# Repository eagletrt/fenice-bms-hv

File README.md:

# Fenice BMS - hardware

## Libraries
The projects don't include the libraries since they use the KiCAD official ones.
Set accordingly the variables `${KICAD_SYMBOL_DIR}` and `${KISYSMOD}` for 
`kicad-symbols` and `kicad-footprints` respectively.
**For `kicad-symbols` checkout the repo to `v5` for now to have the legacy ones.**

Don't rescue symbols!

## Repo structure
```
fenice-bms-hv:hw-master
|-- docs/       # Docs and datasheets of common interest
|-- mainboard/  # MainBoard hardware project folder
|-- cellboard/  # CellBoard hardware project folder
```

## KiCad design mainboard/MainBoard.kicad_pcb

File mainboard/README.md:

# MainBoard
Formula SAE - unitn

## Authors
Latest first:
- Filippo Volpe
- Franco Tabarelli
- Not clear

## Project structure
```
mainboard/
|-- MainBoard.pro           # Project file
|-- MainBoard.sch           # Schematic root
|-- MainShutdown.sch        # Analog shutdown logic schematic
|-- MCU.sch                 # MCU schematic
|-- HVSide.sch              # High voltage monitoring schematic
|-- MainBoard.kicad_pcb     # Board layout file
|-- MainBoard-cache.lib     # Local cache of symbols
|-- fp-info-cache           # Cache of footprints
|-- fp-lib-table            # List of footprint lib files
|-- sym-lib-table           # List of symbols lib files
|-- gerber/                 # Gerbers outputs
|-- netlists/               # Netlists outputs
|-- images/                 # Board renders and such
|-- docs/                   # Additional related documents and outputs
|   |-- hv-bms-mainboard.md # Report/documentation
|-- bom/                    # BOM folder
```

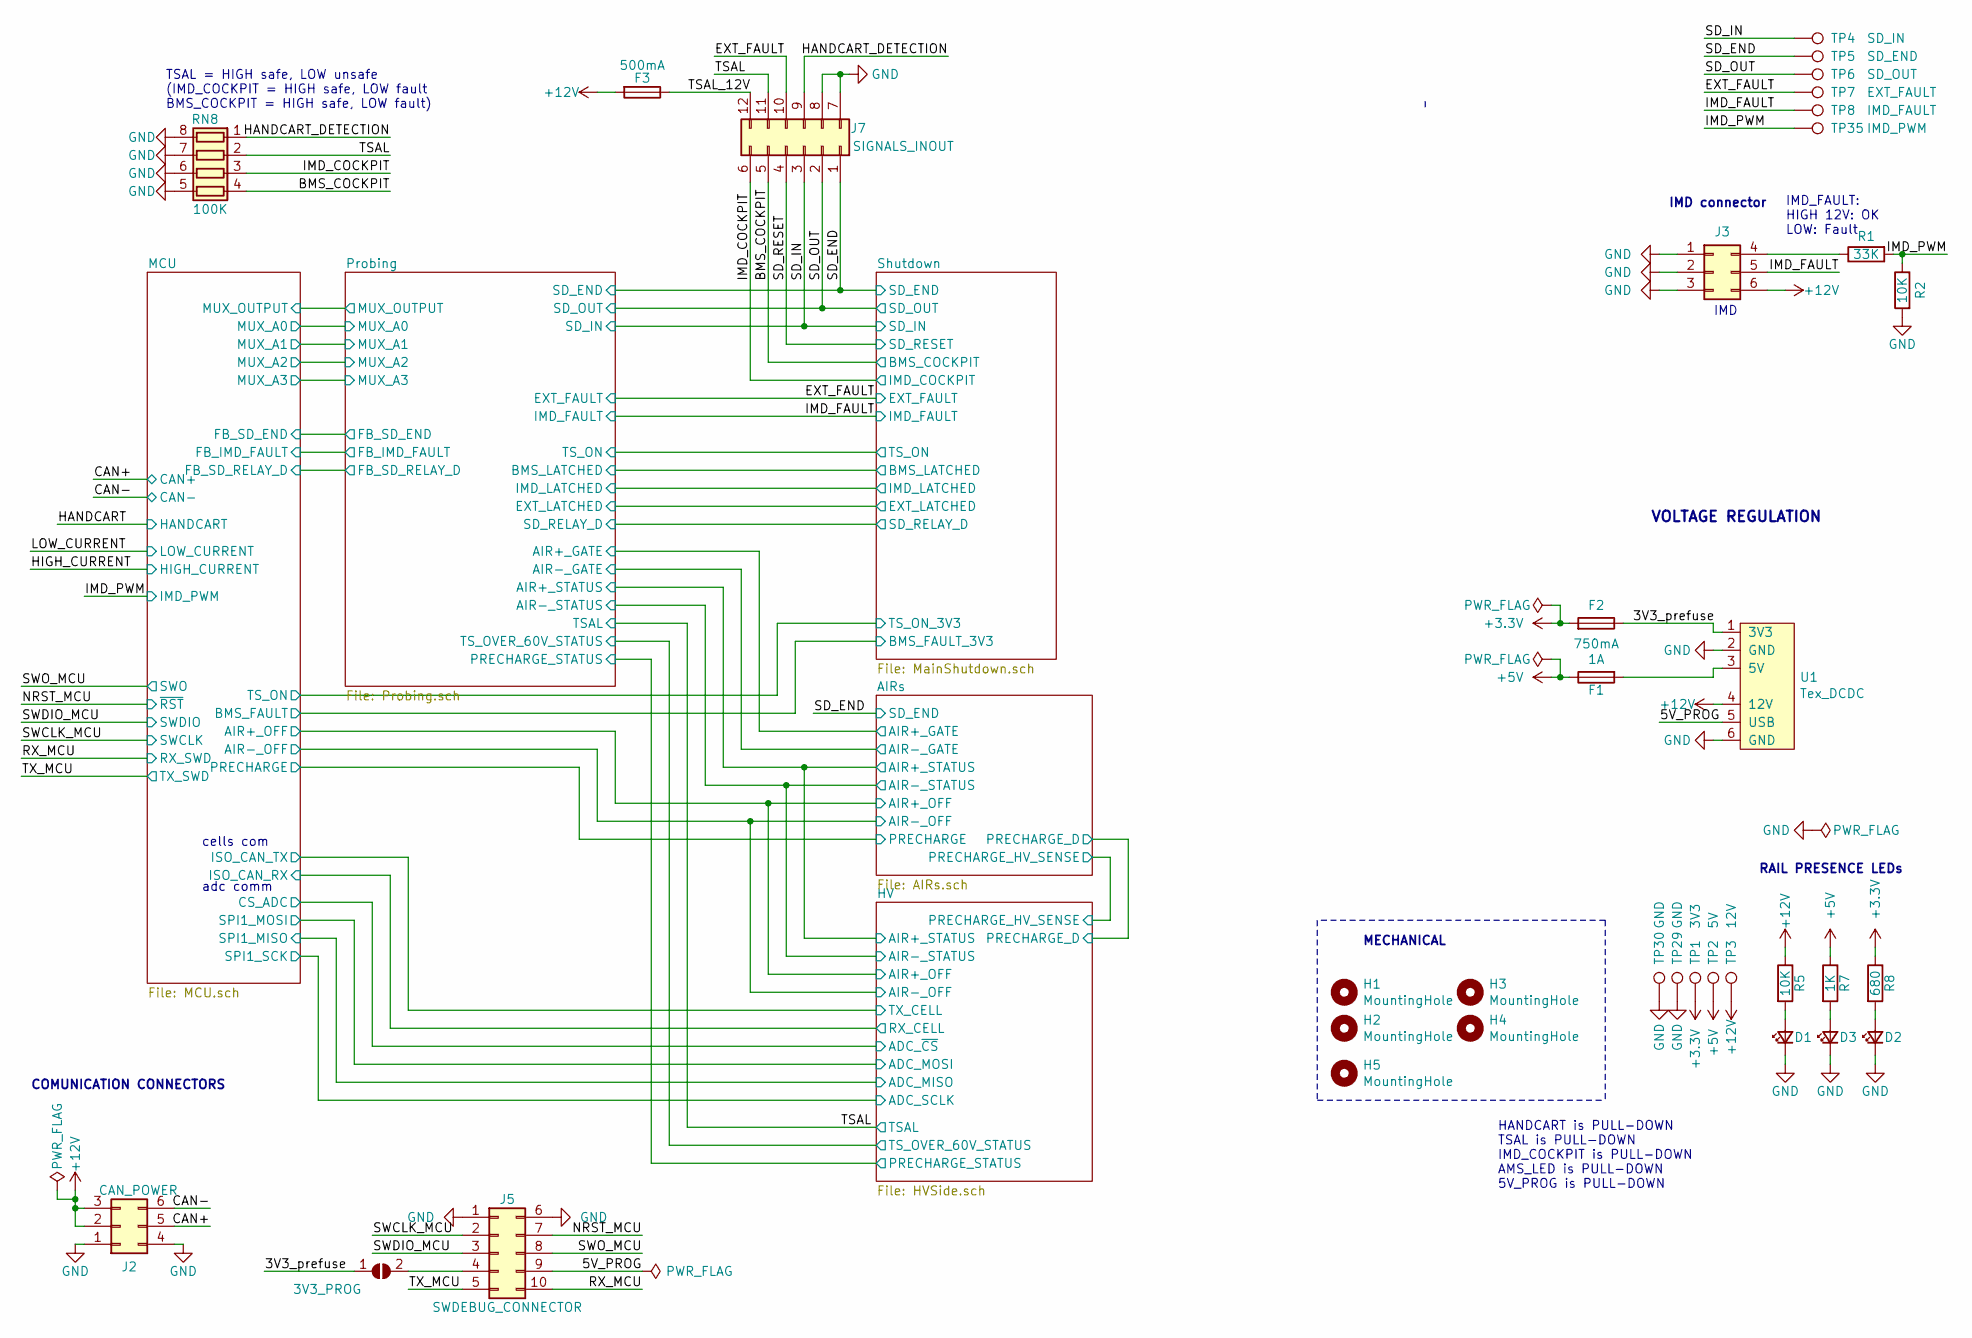
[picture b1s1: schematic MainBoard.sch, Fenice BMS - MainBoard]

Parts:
D1, D2, D3: LED_Small; LED_0603_1608Metric_Castellated
F1: 1A; Fuse_0805_2012Metric
F2: 750mA; Fuse_0805_2012Metric
F3: 500mA; Fuse_1812_4532Metric
H1, H2, H3, H4, H5: MountingHole; MountingHole_3.2_6.1Free
J2: CAN_POWER; Molex_Micro-Fit_3.0_43045-0612_2x03_P3.00mm_Vertical
J3: CONN_2X3; Molex_Micro-Fit_3.0_43045-0612_2x03_P3.00mm_Vertical
J5: SWDEBUG_CONNECTOR; Molex_Nano-Fit_105310-xx10_2x05_P2.50mm_Vertical
J7: SIGNALS_INOUT; Molex_Micro-Fit_3.0_43045-1212_2x06_P3.00mm_Vertical
JP2: 3V3_PROG; SolderJumper-2_P1.3mm_Open_RoundedPad1.0x1.5mm
R1: 33K; R_0603_1608Metric
R2, R5: 10K; R_0603_1608Metric
R7: 1K; R_0603_1608Metric
R8: 680; R_0603_1608Metric
RN8: 100K; R_Array_Convex_4x0603
TP1: 3V3; TestPoint_Pad_D1.0mm
TP2: 5V; TestPoint_Pad_D1.0mm
TP3: 12V; TestPoint_Pad_D1.0mm
TP4: SD_IN; TestPoint_Pad_D1.0mm
TP5: SD_END; TestPoint_Pad_D1.0mm
TP6: SD_OUT; TestPoint_Pad_D1.0mm
TP7: EXT_FAULT; TestPoint_Pad_D1.0mm
TP8: IMD_FAULT; TestPoint_Pad_D1.0mm
TP29, TP30: GND; TestPoint_GNDedge
TP35: IMD_PWM; TestPoint_Pad_D1.0mm
U1: Tex_DCDC; Tex_DCDC_vertical_up

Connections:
+5V: F1.1, R7.1, TP2.1; also elsewhere on the board
+12V: F3.2, J2.2, J2.3, J3.6, R5.1, TP3.1, U1.4 (12V); also elsewhere on the board
/3V3_prefuse: F2.1, JP2.1 (A), U1.1 (3V3)
/5V_PROG: J5.9, U1.5 (USB)
/BMS_COCKPIT: J7.5, RN8.4 (R4.1); also elsewhere on the board
/CAN+: J2.5; also elsewhere on the board
/CAN-: J2.6; also elsewhere on the board
/EXT_FAULT: J7.10, TP7.1; also elsewhere on the board
/HANDCART_DETECTION: J7.9, RN8.1 (R1.1)
/IMD_COCKPIT: J7.6, RN8.3 (R3.1); also elsewhere on the board
/IMD_FAULT: J3.5, TP8.1; also elsewhere on the board
/IMD_PWM: R1.2, R2.1, TP35.1; also elsewhere on the board
/NRST_MCU: J5.7; also elsewhere on the board
/RX_MCU: J5.10; also elsewhere on the board
/SD_END: J7.1, TP5.1; also elsewhere on the board
/SD_IN: J7.3, TP4.1; also elsewhere on the board
/SD_OUT: J7.2, TP6.1; also elsewhere on the board
/SD_RESET: J7.4; also elsewhere on the board
/SWCLK_MCU: J5.2; also elsewhere on the board
/SWDIO_MCU: J5.3; also elsewhere on the board
/SWO_MCU: J5.8; also elsewhere on the board
/TSAL: J7.11, RN8.2 (R2.1); also elsewhere on the board
/TSAL_12V: F3.1, J7.12
/TX_MCU: J5.5; also elsewhere on the board
GND: D1.1 (K), D2.1 (K), D3.1 (K), J2.1, J2.4, J3.1, J3.2, J3.3, J5.1, J5.6, J7.7, J7.8, R2.2, RN8.5 (R4.2), RN8.6 (R3.2), RN8.7 (R2.2), RN8.8 (R1.2), TP29.1, TP30.1, U1.2 (GND), U1.6 (GND); also elsewhere on the board
unnamed: D1.2 (A), R5.2
unnamed: D2.2 (A), R8.2
unnamed: D3.2 (A), R7.2
unnamed: F1.2, U1.3 (5V)
unnamed: J3.4, R1.1
unnamed: J5.4, JP2.2 (B)

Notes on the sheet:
IMD
IMD connector
COMUNICATION CONNECTORS
MECHANICAL
IMD_FAULT: HIGH 12V: OK LOW: Fault
adc comm
TSAL = HIGH safe, LOW unsafe (IMD_COCKPIT = HIGH safe, LOW fault BMS_COCKPIT = HIGH safe, LOW fault)
cells com
HANDCART is PULL-DOWN TSAL is PULL-DOWN IMD_COCKPIT is PULL-DOWN AMS_LED is PULL-DOWN 5V_PROG is PULL-DOWN
VOLTAGE REGULATION
RAIL PRESENCE LEDs

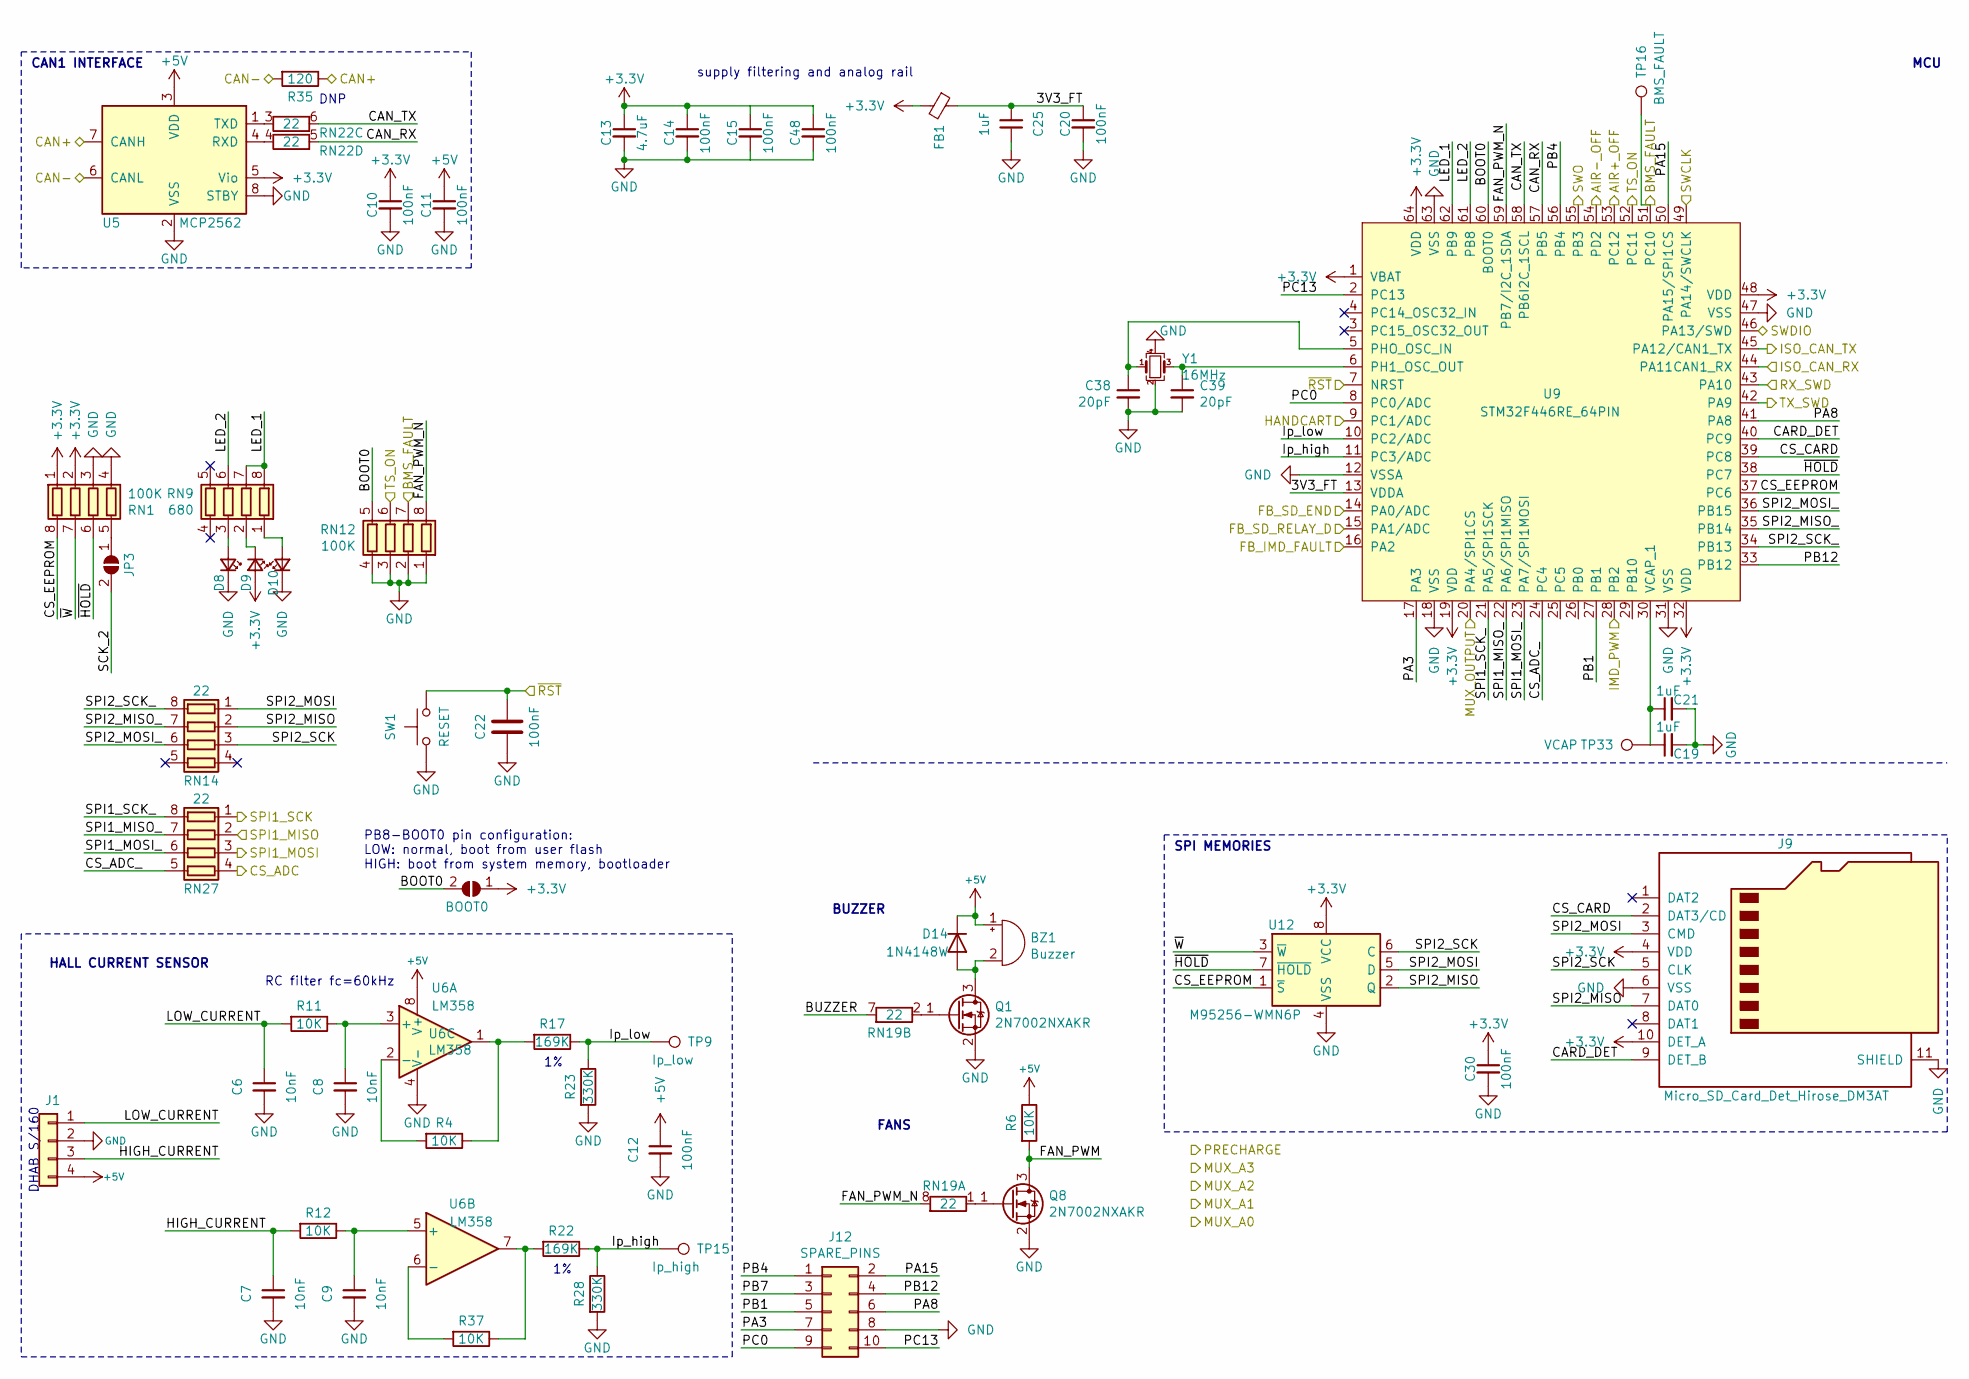
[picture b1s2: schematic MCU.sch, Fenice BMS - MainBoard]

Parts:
BZ1: Buzzer; Buzzer_TDK_SD1614TT_D16mm_H14mm_P5mm
C6, C7, C8, C9: 10nF; C_0603_1608Metric
C10, C11, C12, C14, C15, C20, C22, C30, C48: 100nF; C_0603_1608Metric
C13: 4.7uF; C_0805_2012Metric
C19, C21, C25: 1uF; C_0805_2012Metric
C38, C39: 20pF; C_0603_1608Metric
D8: LED_Small; LED_reverse_mount_cilindrical
D9, D10: LED_Small; LED_0603_1608Metric_Castellated
D14: 1N4148W; D_SOD-123
FB1: FerriteBead_Small; L_0603_1608Metric_Pad1.05x0.95mm_HandSolder
J1: CONN_1x4; Molex_Micro-Fit_3.0_43650-0415_1x04_P3.00mm_Vertical
J9: Micro_SD_Card_Det_Hirose_DM3AT; microSD_HC_Hirose_DM3AT-SF-PEJM5
J12: SPARE_PINS; PinHeader_2x05_P2.54mm_Vertical
JP1: BOOT0; SolderJumper-2_P1.3mm_Open_RoundedPad1.0x1.5mm
JP3: SolderJumper_2_Open; SolderJumper-2_P1.3mm_Open_RoundedPad1.0x1.5mm
Q1, Q8: 2N7002NXAKR; SOT-23
R4, R6, R11, R12, R37: 10K; R_0603_1608Metric
R17, R22: 169K; R_0603_1608Metric
R23, R28: 330K; R_0603_1608Metric
R35: 120; R_0805_2012Metric
RN1, RN12: 100K; R_Array_Convex_4x0603
RN9: 680; R_Array_Convex_4x0603
RN14, RN19, RN22, RN27: 22; R_Array_Convex_4x0603
SW1: RESET; SW_SPST_FSMSM
TP9: Ip_low; TestPoint_Pad_D1.0mm
TP15: Ip_high; TestPoint_Pad_D1.0mm
TP16: BMS_FAULT; TestPoint_Pad_D1.0mm
TP33: VCAP; TestPoint_Pad_D1.0mm
U5: MCP2562; SOIC-8_3.9x4.9mm_P1.27mm
U6: LM358; TSOT-23-8
U9: STM32F446RE_64PIN; LQFP-64_10x10mm_P0.5mm
U12: M95256-WMN6P; TSSOP-8_4.4x3mm_P0.65mm
Y1: 16MHz; Crystal_SMD_3225-4Pin_3.2x2.5mm

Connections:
+5V: BZ1.1 (-), C11.1, C12.1, D14.1 (K), J1.4, R6.1, U5.3 (VDD), U6.8 (V+); also elsewhere on the board
/AIRs/AIR+_OFF: U9.53 (PC12); also elsewhere on the board
/AIRs/AIR-_OFF: U9.54 (PD2); also elsewhere on the board
/CAN+: R35.1, U5.7 (CANH); also elsewhere on the board
/CAN-: R35.2, U5.6 (CANL); also elsewhere on the board
/HANDCART: U9.9 (PC1/ADC)
/HV/ADC_MISO: RN27.2 (R2.1); also elsewhere on the board
/HV/ADC_MOSI: RN27.3 (R3.1); also elsewhere on the board
/HV/ADC_SCLK: RN27.1 (R1.1); also elsewhere on the board
/HV/ADC_~CS~: RN27.4 (R4.1); also elsewhere on the board
/IMD_PWM: U9.28 (PB2); also elsewhere on the board
/MCU/3V3_FT: C20.1, C25.2, FB1.1, U9.13 (VDDA)
/MCU/BMS_FAULT: RN12.7 (R2.2), TP16.1, U9.51 (PC10); also elsewhere on the board
/MCU/BOOT0: JP1.2 (B), RN12.5 (R4.2), U9.60 (BOOT0)
/MCU/BUZZER: RN19.7 (R2.2)
/MCU/CAN_RX: RN22.5 (R4.2), U9.57 (PB5)
/MCU/CAN_TX: RN22.6 (R3.2), U9.58 (PB6I2C_1SCL)
/MCU/CARD_DET: J9.9 (DET_B), U9.40 (PC9)
/MCU/CS_ADC_: RN27.5 (R4.2), U9.24 (PC4)
/MCU/CS_CARD: J9.2 (DAT3/CD), U9.39 (PC8)
/MCU/CS_EEPROM: RN1.8 (R1.2), U9.37 (PC6), U12.1 (~S)
/MCU/FAN_PWM: Q8.3 (D), R6.2
/MCU/FAN_PWM_N: RN12.8 (R1.2), RN19.8 (R1.2), U9.59 (PB7/I2C_1SDA)
/MCU/FB_IMD_FAULT: U9.16 (PA2)
/MCU/FB_SD_END: U9.14 (PA0/ADC); also elsewhere on the board
/MCU/FB_SD_RELAY_D: U9.15 (PA1/ADC)
/MCU/HIGH_CURRENT: C7.1, J1.3, R12.2
/MCU/ISO_CAN_RX: U9.44 (PA11CAN1_RX); also elsewhere on the board
/MCU/ISO_CAN_TX: U9.45 (PA12/CAN1_TX); also elsewhere on the board
/MCU/Ip_high: R22.1, R28.1, TP15.1, U9.11 (PC3/ADC)
/MCU/Ip_low: R17.1, R23.1, TP9.1, U9.10 (PC2/ADC)
/MCU/LED_1: RN9.7 (R2.2), RN9.8 (R1.2), U9.62 (PB9)
/MCU/LED_2: RN9.6 (R3.2), U9.61 (PB8)
/MCU/LOW_CURRENT: C6.1, J1.1, R11.2
/MCU/MUX_OUTPUT: U9.20 (PA4/SPI1CS); also elsewhere on the board
/MCU/PA3: J12.7, U9.17 (PA3)
/MCU/PA8: J12.6, U9.41 (PA8)
/MCU/PA15: J12.2, U9.50 (PA15/SPI1CS)
/MCU/PB1: J12.5, U9.27 (PB1)
/MCU/PB4: J12.1, U9.56 (PB4)
/MCU/PB7: J12.3
/MCU/PB12: J12.4, U9.33 (PB12)
/MCU/PC0: J12.9, U9.8 (PC0/ADC)
/MCU/PC13: J12.10, U9.2 (PC13)
/MCU/SCK_2: JP3.2 (B)
/MCU/SPI1_MISO_: RN27.7 (R2.2), U9.22 (PA6/SPI1MISO)
/MCU/SPI1_MOSI_: RN27.6 (R3.2), U9.23 (PA7/SPI1MOSI)
/MCU/SPI1_SCK_: RN27.8 (R1.2), U9.21 (PA5/SPI1SCK)
/MCU/SPI2_MISO: J9.7 (DAT0), RN14.2 (R2.1), U12.2 (Q)
/MCU/SPI2_MISO_: RN14.7 (R2.2), U9.35 (PB14)
/MCU/SPI2_MOSI: J9.3 (CMD), RN14.1 (R1.1), U12.5 (D)
/MCU/SPI2_MOSI_: RN14.6 (R3.2), U9.36 (PB15)
/MCU/SPI2_SCK: J9.5 (CLK), RN14.3 (R3.1), U12.6 (C)
/MCU/SPI2_SCK_: RN14.8 (R1.2), U9.34 (PB13)
/MCU/TS_ON: RN12.6 (R3.2), U9.52 (PC11); also elsewhere on the board
/MCU/~HOLD~: RN1.6 (R3.2), U9.38 (PC7), U12.7 (~HOLD)
/MCU/~W~: RN1.7 (R2.2), U12.3 (~W)
/NRST_MCU: C22.1, SW1.1, U9.7 (NRST); also elsewhere on the board
/RX_MCU: U9.43 (PA10); also elsewhere on the board
/SWCLK_MCU: U9.49 (PA14/SWCLK); also elsewhere on the board
/SWDIO_MCU: U9.46 (PA13/SWD); also elsewhere on the board
/SWO_MCU: U9.55 (PB3); also elsewhere on the board
/TX_MCU: U9.42 (PA9); also elsewhere on the board
GND: C6.2, C7.2, C8.2, C9.2, C10.2, C11.2, C12.2, C13.2, C14.2, C15.2, C19.2, C20.2, C21.2, C22.2, C25.1, C30.2, C38.2, C39.2, C48.2, D8.1 (K), D10.1 (K), J1.2, J9.6 (VSS), J9.11 (SHIELD), J12.8, Q1.2 (S), Q8.2 (S), R23.2, R28.2, RN1.3 (R3.1), RN1.4 (R4.1), RN12.1 (R1.1), RN12.2 (R2.1), RN12.3 (R3.1), RN12.4 (R4.1), SW1.2, U5.2 (VSS), U5.8 (STBY), U6.4 (V-), U9.12 (VSSA), U9.18 (VSS), U9.31 (VSS), U9.47 (VSS), U9.63 (VSS), U12.4 (VSS), Y1.2, Y1.4; also elsewhere on the board
unnamed: BZ1.2 (+), D14.2 (A), Q1.3 (D)
unnamed: C8.1, R11.1, U6.3 (+)
unnamed: C9.1, R12.1, U6.5 (+)
unnamed: C19.1, C21.1, TP33.1, U9.30 (VCAP_1)
unnamed: C38.1, U9.5 (PHO_OSC_IN), Y1.1
unnamed: C39.1, U9.6 (PH1_OSC_OUT), Y1.3
unnamed: D8.2 (A), RN9.3 (R3.1)
unnamed: D9.1 (K), RN9.2 (R2.1)
unnamed: D10.2 (A), RN9.1 (R1.1)
unnamed: JP3.1 (A), RN1.5 (R4.2)
unnamed: Q1.1 (G), RN19.2 (R2.1)
unnamed: Q8.1 (G), RN19.1 (R1.1)
unnamed: R4.2, U6.2 (-)
unnamed: R4.1, R17.2, U6.1
unnamed: R22.2, R37.1, U6.7
unnamed: R37.2, U6.6 (-)
unnamed: RN22.3 (R3.1), U5.1 (TXD)
unnamed: RN22.4 (R4.1), U5.4 (RXD)

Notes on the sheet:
CAN1 INTERFACE
HALL CURRENT SENSOR
MCU
supply filtering and analog rail
SPI MEMORIES
PB8-BOOT0 pin configuration: LOW: normal, boot from user flash HIGH: boot from system memory, bootloader
DHAB S/160
RC filter fc=60kHz
DNP
FANS
BUZZER

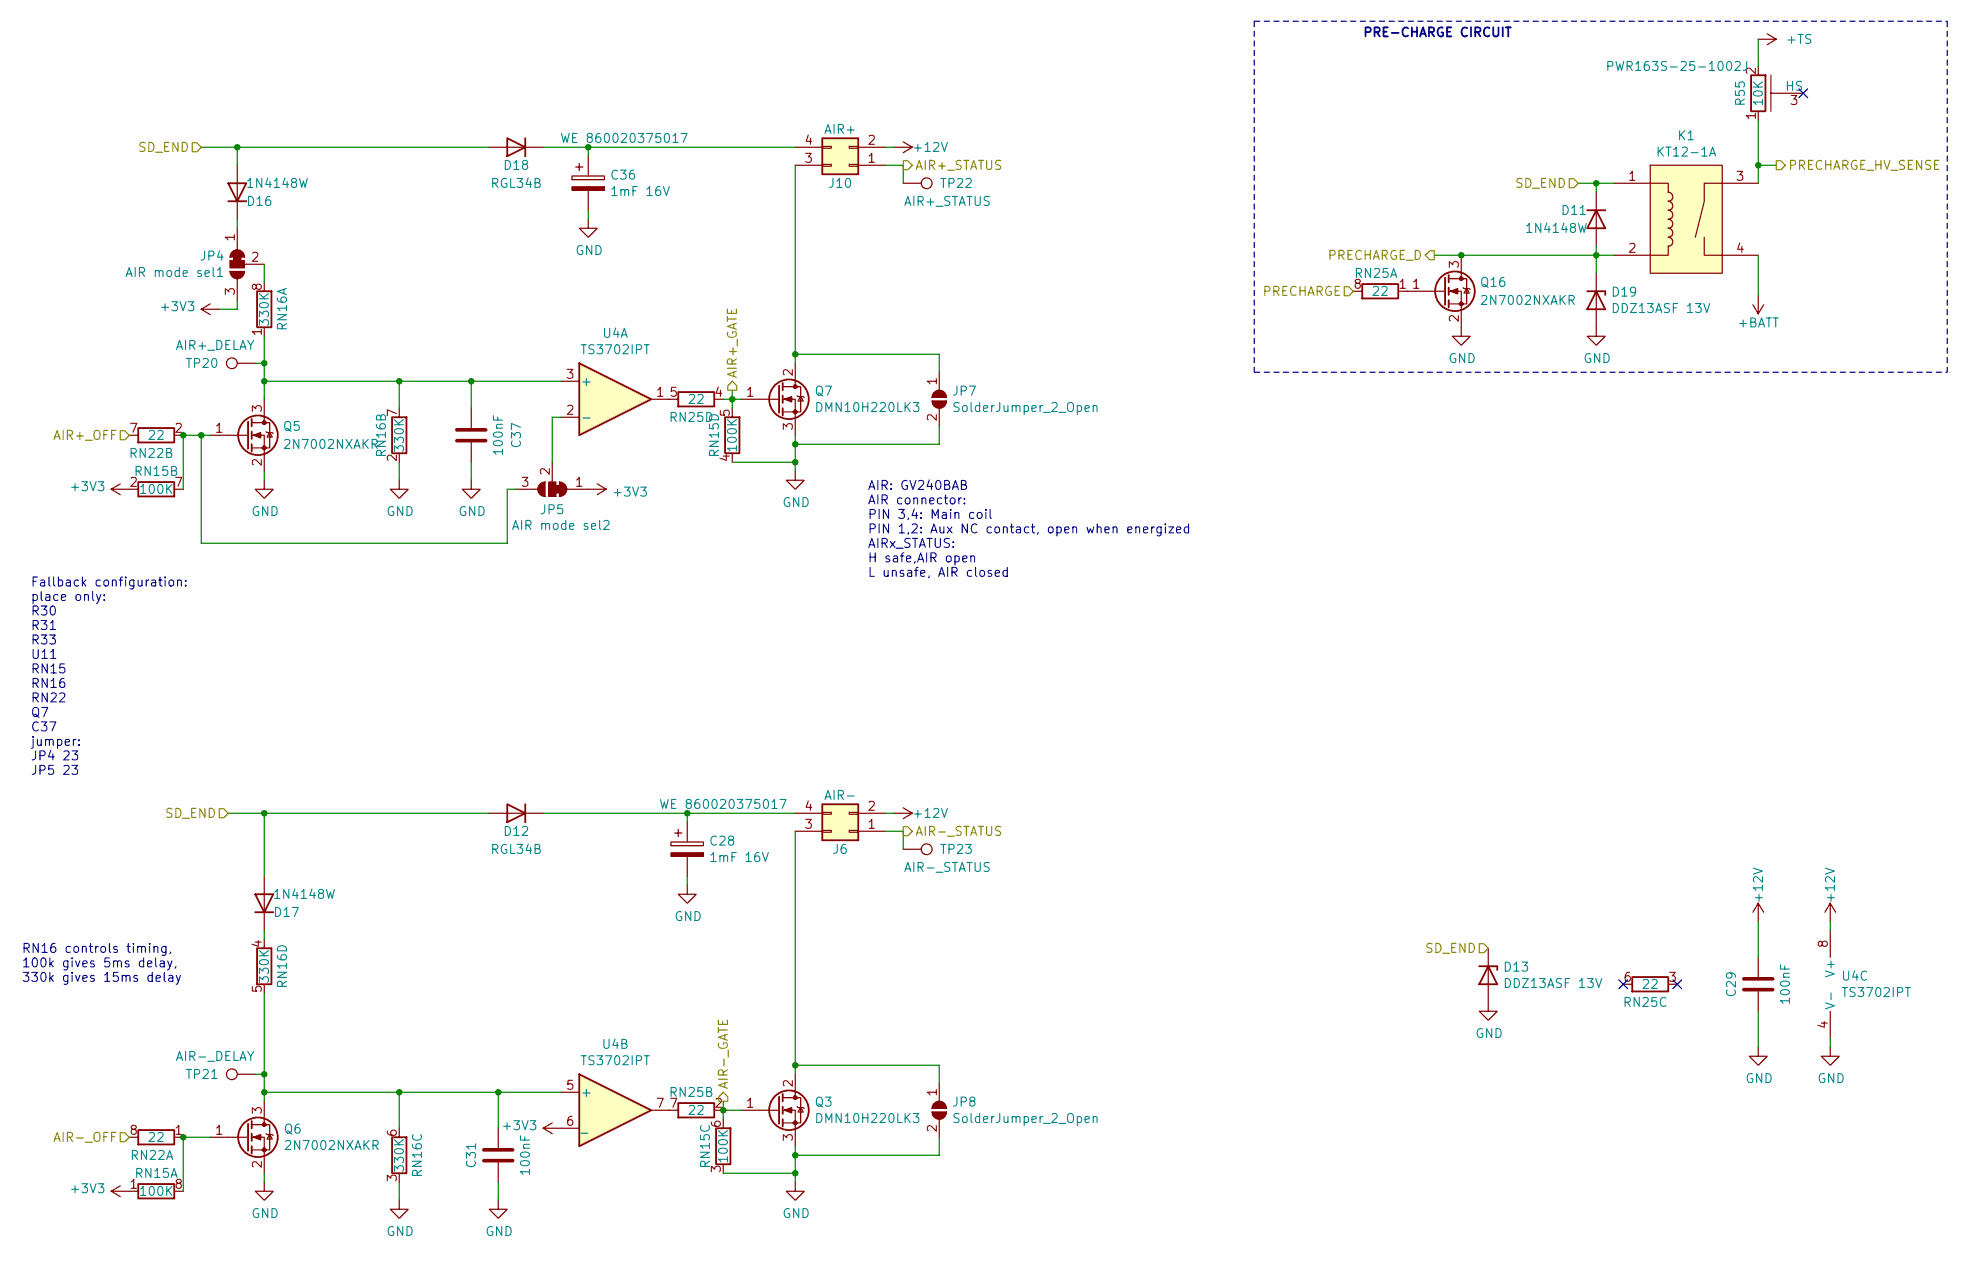
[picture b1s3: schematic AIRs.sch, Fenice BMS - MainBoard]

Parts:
C28, C36: 1mF 16V; CP_Radial_D10.0mm_P5.00mm; Partname WE 860020375017
C29, C31, C37: 100nF; C_0603_1608Metric
D11, D16, D17: 1N4148W; D_SOD-123
D12, D18: RGL34B; D_MiniMELF
D13, D19: DDZ13ASF 13V; D_SOD-323
J6: AIR-; Molex_Micro-Fit_3.0_43045-0412_2x02_P3.00mm_Vertical
J10: AIR+; Molex_Micro-Fit_3.0_43045-0412_2x02_P3.00mm_Vertical
JP4: AIR mode sel1; SolderJumper-3_P1.3mm_Bridged12_RoundedPad1.0x1.5mm
JP5: AIR mode sel2; SolderJumper-3_P1.3mm_Bridged12_RoundedPad1.0x1.5mm
JP7, JP8: SolderJumper_2_Open; SolderJumper-2_P1.3mm_Open_RoundedPad1.0x1.5mm
K1: KT12-1A; KT12_THT
Q3, Q7: DMN10H220LK3; TO-252-2
Q5, Q6, Q16: 2N7002NXAKR; SOT-23
R55: 10K; PWR163; Partname PWR163S-25-1002J
RN15: 100K; R_Array_Convex_4x0603
RN16: 330K; R_Array_Convex_4x0603
RN22, RN25: 22; R_Array_Convex_4x0603
TP20: AIR+_DELAY; TestPoint_Pad_D1.0mm
TP21: AIR-_DELAY; TestPoint_Pad_D1.0mm
TP22: AIR+_STATUS; TestPoint_Pad_D1.0mm
TP23: AIR-_STATUS; TestPoint_Pad_D1.0mm
U4: TS3702IPT; TSSOP-8_4.4x3mm_P0.65mm

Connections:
+12V: C29.1, J6.2, J10.2, U4.8 (V+); also elsewhere on the board
+BATT: K1.4; also elsewhere on the board
+TS: R55.2; also elsewhere on the board
/AIRs/AIR+_GATE: Q7.1 (G), RN15.5 (R4.2), RN25.4 (R4.1); also elsewhere on the board
/AIRs/AIR+_OFF: RN22.7 (R2.2); also elsewhere on the board
/AIRs/AIR+_STATUS: J10.1, TP22.1; also elsewhere on the board
/AIRs/AIR-_GATE: Q3.1 (G), RN15.6 (R3.2), RN25.2 (R2.1); also elsewhere on the board
/AIRs/AIR-_OFF: RN22.8 (R1.2); also elsewhere on the board
/AIRs/AIR-_STATUS: J6.1, TP23.1; also elsewhere on the board
/AIRs/PRECHARGE: RN25.8 (R1.2)
/AIRs/PRECHARGE_D: D11.2 (A), D19.1 (K), K1.2, Q16.3 (D); also elsewhere on the board
/AIRs/PRECHARGE_HV_SENSE: K1.3, R55.1; also elsewhere on the board
/SD_END: D11.1 (K), D12.2 (A), D13.1 (K), D16.2 (A), D17.2 (A), D18.2 (A), K1.1; also elsewhere on the board
GND: C28.2, C29.2, C31.2, C36.2, C37.2, D13.2 (A), D19.2 (A), JP7.2 (B), JP8.2 (B), Q3.3 (S), Q5.2 (S), Q6.2 (S), Q7.3 (S), Q16.2 (S), RN15.3 (R3.1), RN15.4 (R4.1), RN16.2 (R2.1), RN16.3 (R3.1), U4.4 (V-); also elsewhere on the board
unnamed: C28.1, D12.1 (K), J6.4
unnamed: C31.1, Q6.3 (D), RN16.5 (R4.2), RN16.6 (R3.2), TP21.1, U4.5 (+)
unnamed: C36.1, D18.1 (K), J10.4
unnamed: C37.1, Q5.3 (D), RN16.1 (R1.1), RN16.7 (R2.2), TP20.1, U4.3 (+)
unnamed: D16.1 (K), JP4.1 (A)
unnamed: D17.1 (K), RN16.4 (R4.1)
unnamed: J6.3, JP8.1 (A), Q3.2 (D)
unnamed: J10.3, JP7.1 (A), Q7.2 (D)
unnamed: JP4.2 (C), RN16.8 (R1.2)
unnamed: JP5.2 (C), U4.2 (-)
unnamed: JP5.3 (B), Q5.1 (G), RN15.7 (R2.2), RN22.2 (R2.1)
unnamed: Q6.1 (G), RN15.8 (R1.2), RN22.1 (R1.1)
unnamed: Q16.1 (G), RN25.1 (R1.1)
unnamed: RN25.5 (R4.2), U4.1
unnamed: RN25.7 (R2.2), U4.7

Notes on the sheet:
AIR: GV240BAB AIR connector: PIN 3,4: Main coil PIN 1,2: Aux NC contact, open when energized AIRx_STATUS: H safe,AIR open L unsafe, AIR closed
PRE-CHARGE CIRCUIT
RN16 controls timing, 100k gives 5ms delay, 330k gives 15ms delay
Fallback configuration: place only: R30 R31 R33 U11 RN15 RN16 RN22 Q7 C37 jumper: JP4 23 JP5 23

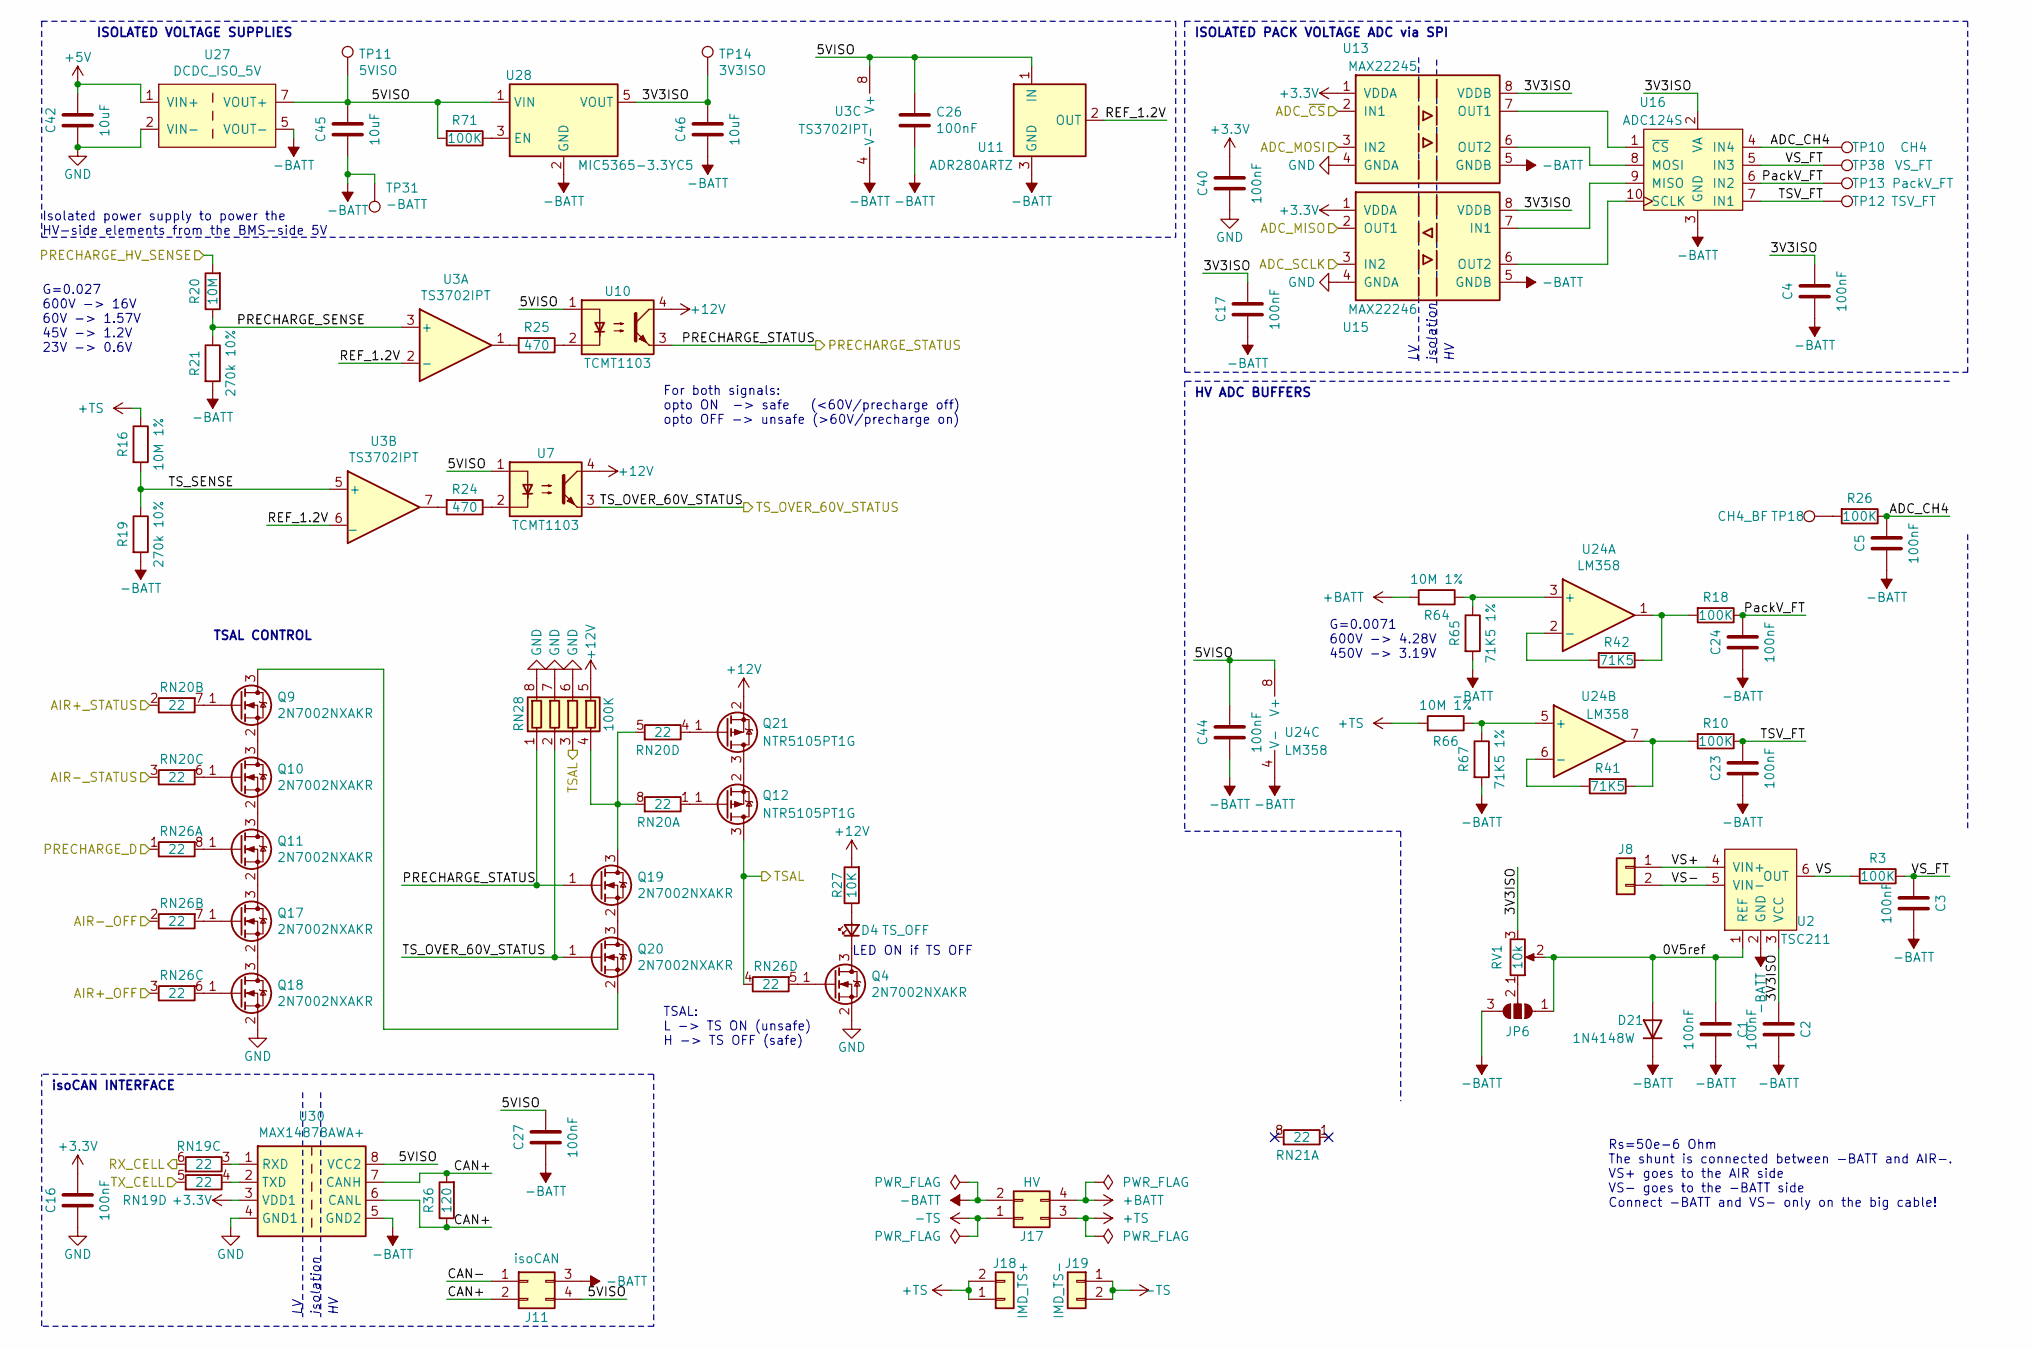
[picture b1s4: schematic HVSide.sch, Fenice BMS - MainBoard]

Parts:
C1, C2, C3, C4, C5, C16, C17, C23, C24, C26, C27, C40, C44: 100nF; C_0603_1608Metric
C42, C45, C46: 10uF; C_0805_2012Metric
D4: TS_OFF; LED_0603_1608Metric_Castellated
D21: 1N4148W; D_SOD-123
J8: CONN_1X2; Molex_Micro-Fit_3.0_43650-0215_1x02_P3.00mm_Vertical
J11: isoCAN; Molex_Micro-Fit_3.0_43045-0412_2x02_P3.00mm_Vertical
J17: HV; Molex_Mega-Fit_76829-0104_2x02_P5.70mm_Vertical
J18: IMD_TS+; Molex_Micro-Fit_3.0_43650-0215_1x02_P3.00mm_Vertical
J19: IMD_TS-; Molex_Micro-Fit_3.0_43650-0215_1x02_P3.00mm_Vertical
JP6: SolderJumper_3_Open; SolderJumper-3_P1.3mm_Open_RoundedPad1.0x1.5mm
Q4, Q9, Q10, Q11, Q17, Q18, Q19, Q20: 2N7002NXAKR; SOT-23
Q12, Q21: NTR5105PT1G; SOT-23
R3, R10, R18, R26, R71: 100K; R_0603_1608Metric
R16, R64, R66: 10M 1%; R_2010_5025Metric
R19, R21: 270k 10%; R_0603_1608Metric
R20: 10M; R_2010_5025Metric
R24, R25: 470; R_0603_1608Metric
R27: 10K; R_0603_1608Metric
R36: 120; R_0805_2012Metric
R41, R42: 71K5; R_0603_1608Metric
R65, R67: 71K5 1%; R_0603_1608Metric
RN19, RN20, RN21, RN26: 22; R_Array_Convex_4x0603
RN28: 100K; R_Array_Convex_4x0603
RV1: 10k; Potentiometer_Bourns_3314J_Vertical
TP10: CH4; TestPoint_Pad_D1.0mm
TP11: 5VISO; TestPoint_Pad_D1.0mm
TP12: TSV_FT; TestPoint_Pad_D1.0mm
TP13: PackV_FT; TestPoint_Pad_D1.0mm
TP14: 3V3ISO; TestPoint_Pad_D1.0mm
TP18: CH4_BF; TestPoint_Pad_D1.0mm
TP31: -BATT; TestPoint_GNDedge
TP38: VS_FT; TestPoint_Pad_D1.0mm
U2: TSC211; SOT-363_SC-70-6
U3: TS3702IPT; TSSOP-8_4.4x3mm_P0.65mm
U7, U10: TCMT1103; SOP-4_4.4x2.6mm_P1.27mm
U11: ADR280ARTZ; SOT-23
U13: MAX22245; SOIC-8_7.5x5.85mm_P1.27mm
U15: MAX22246; SOIC-8_7.5x5.85mm_P1.27mm
U16: ADC124S; VSSOP-10_3x3mm_P0.5mm
U24: LM358; TSOT-23-8
U27: DCDC_ISO_5V; RFMM_0505S
U28: MIC5365-3.3YC5; SOT-353_SC-70-5
U30: MAX14878AWA+; SOIC-8W_5.3x5.3mm_P1.27mm

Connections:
+5V: C42.1, U27.1 (VIN+); also elsewhere on the board
+12V: Q21.2 (S), R27.2, RN28.5 (R4.2), U7.4, U10.4; also elsewhere on the board
+BATT: J17.4, R64.2; also elsewhere on the board
+TS: J17.3, J18.1, J18.2, R16.1, R66.2; also elsewhere on the board
-BATT: C1.2, C2.1, C3.1, C4.2, C5.2, C17.2, C23.2, C24.2, C26.2, C27.2, C44.2, C45.2, C46.2, D21.1 (K), J11.3, J17.2, JP6.3 (B), R19.2, R21.2, R65.2, R67.2, TP31.1, U2.2 (GND), U3.4 (V-), U11.3 (GND), U13.5 (GNDB), U15.5 (GNDB), U16.3 (GND), U24.4 (V-), U27.5 (VOUT-), U28.2 (GND), U30.5 (GND2)
-TS: J17.1, J19.1, J19.2
/AIRs/AIR+_OFF: RN26.3 (R3.1); also elsewhere on the board
/AIRs/AIR+_STATUS: RN20.2 (R2.1); also elsewhere on the board
/AIRs/AIR-_OFF: RN26.2 (R2.1); also elsewhere on the board
/AIRs/AIR-_STATUS: RN20.3 (R3.1); also elsewhere on the board
/AIRs/PRECHARGE_D: RN26.1 (R1.1); also elsewhere on the board
/AIRs/PRECHARGE_HV_SENSE: R20.2; also elsewhere on the board
/HV/0V5ref: C1.1, D21.2 (A), JP6.1 (A), RV1.2, U2.1 (REF)
/HV/3V3ISO: C2.2, C4.1, C17.1, C46.1, RV1.3, TP14.1, U2.3 (VCC), U13.8 (VDDB), U15.8 (VDDB), U16.2 (VA), U28.5 (VOUT)
/HV/5VISO: C26.1, C27.1, C44.1, C45.1, J11.4, R71.2, TP11.1, U3.8 (V+), U7.1, U10.1, U11.1 (IN), U24.8 (V+), U27.7 (VOUT+), U28.1 (VIN), U30.8 (VCC2)
/HV/ADC_CH4: C5.1, R26.1, TP10.1, U16.4 (IN4)
/HV/ADC_MISO: U15.2 (OUT1); also elsewhere on the board
/HV/ADC_MOSI: U13.3 (IN2); also elsewhere on the board
/HV/ADC_SCLK: U15.3 (IN2); also elsewhere on the board
/HV/ADC_~CS~: U13.2 (IN1); also elsewhere on the board
/HV/CAN+: J11.2, R36.1, R36.2, U30.6 (CANL), U30.7 (CANH)
/HV/CAN-: J11.1
/HV/PRECHARGE_SENSE: R20.1, R21.1, U3.3 (+)
/HV/PRECHARGE_STATUS: Q19.1 (G), RN28.1 (R1.1), U10.3; also elsewhere on the board
/HV/PackV_FT: C24.1, R18.1, TP13.1, U16.6 (IN2)
/HV/REF_1.2V: U3.2 (-), U3.6 (_), U11.2 (OUT)
/HV/TSV_FT: C23.1, R10.1, TP12.1, U16.7 (IN1)
/HV/TS_OVER_60V_STATUS: Q20.1 (G), RN28.2 (R2.1), U7.3; also elsewhere on the board
/HV/TS_SENSE: R16.2, R19.1, U3.5 (+)
/HV/VS: R3.2, U2.6 (OUT)
/HV/VS+: J8.1, U2.4 (VIN+)
/HV/VS-: J8.2, U2.5 (VIN-)
/HV/VS_FT: C3.2, R3.1, TP38.1, U16.5 (IN3)
/MCU/ISO_CAN_RX: RN19.6 (R3.2); also elsewhere on the board
/MCU/ISO_CAN_TX: RN19.5 (R4.2); also elsewhere on the board
/TSAL: Q12.3 (D), RN26.4 (R4.1), RN28.3 (R3.1); also elsewhere on the board
GND: C16.2, C40.2, C42.2, Q4.2 (S), Q18.2 (S), RN28.6 (R3.2), RN28.7 (R2.2), RN28.8 (R1.2), U13.4 (GNDA), U15.4 (GNDA), U27.2 (VIN-), U30.4 (GND1); also elsewhere on the board
unnamed: D4.1 (K), Q4.3 (D)
unnamed: D4.2 (A), R27.1
unnamed: JP6.2 (C), RV1.1
unnamed: Q4.1 (G), RN26.5 (R4.2)
unnamed: Q9.1 (G), RN20.7 (R2.2)
unnamed: Q10.1 (G), RN20.6 (R3.2)
unnamed: Q10.2 (S), Q11.3 (D)
unnamed: Q9.2 (S), Q10.3 (D)
unnamed: Q11.1 (G), RN26.8 (R1.2)
unnamed: Q11.2 (S), Q17.3 (D)
unnamed: Q12.1 (G), RN20.1 (R1.1)
unnamed: Q12.2 (S), Q21.3 (D)
unnamed: Q17.1 (G), RN26.7 (R2.2)
unnamed: Q17.2 (S), Q18.3 (D)
unnamed: Q18.1 (G), RN26.6 (R3.2)
unnamed: Q19.2 (S), Q20.3 (D)
unnamed: Q19.3 (D), RN20.5 (R4.2), RN20.8 (R1.2), RN28.4 (R4.1)
unnamed: Q9.3 (D), Q20.2 (S)
unnamed: Q21.1 (G), RN20.4 (R4.1)
unnamed: R10.2, R41.1, U24.7
unnamed: R18.2, R42.1, U24.1
unnamed: R24.1, U7.2
unnamed: R24.2, U3.7
unnamed: R25.1, U10.2
unnamed: R25.2, U3.1
unnamed: R26.2, TP18.1
unnamed: R41.2, U24.6 (-)
unnamed: R42.2, U24.2 (-)
unnamed: R64.1, R65.1, U24.3 (+)
unnamed: R66.1, R67.1, U24.5 (+)
unnamed: R71.1, U28.3 (EN)
unnamed: RN19.3 (R3.1), U30.1 (RXD)
unnamed: RN19.4 (R4.1), U30.2 (TXD)
unnamed: U13.6 (OUT2), U16.8 (MOSI)
unnamed: U13.7 (OUT1), U16.1 (~CS~)
unnamed: U15.6 (OUT2), U16.10 (SCLK)
unnamed: U15.7 (IN1), U16.9 (MISO)

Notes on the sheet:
ISOLATED VOLTAGE SUPPLIES
HV ADC BUFFERS
isoCAN INTERFACE
isolation
Isolated power supply to power the HV-side elements from the BMS-side 5V
Rs=50e-6 Ohm The shunt is connected between -BATT and AIR-. VS+ goes to the AIR side VS- goes to the -BATT side Connect -BATT and VS- only on the big cable!
G=0.0071 600V -> 4.28V 450V -> 3.19V
ISOLATED PACK VOLTAGE ADC via SPI
TSAL CONTROL
LED ON if TS OFF
TSAL: L -> TS ON (unsafe) H -> TS OFF (safe)
G=0.027 600V -> 16V 60V -> 1.57V 45V -> 1.2V 23V -> 0.6V
For both signals: opto ON -> safe (<60V/precharge off) opto OFF -> unsafe (>60V/precharge on)
